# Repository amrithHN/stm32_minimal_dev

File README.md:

# stm32_minimal_dev
 
 Simple stm32f4 minimal dev board built for as part of learning hardware design using kicad 6

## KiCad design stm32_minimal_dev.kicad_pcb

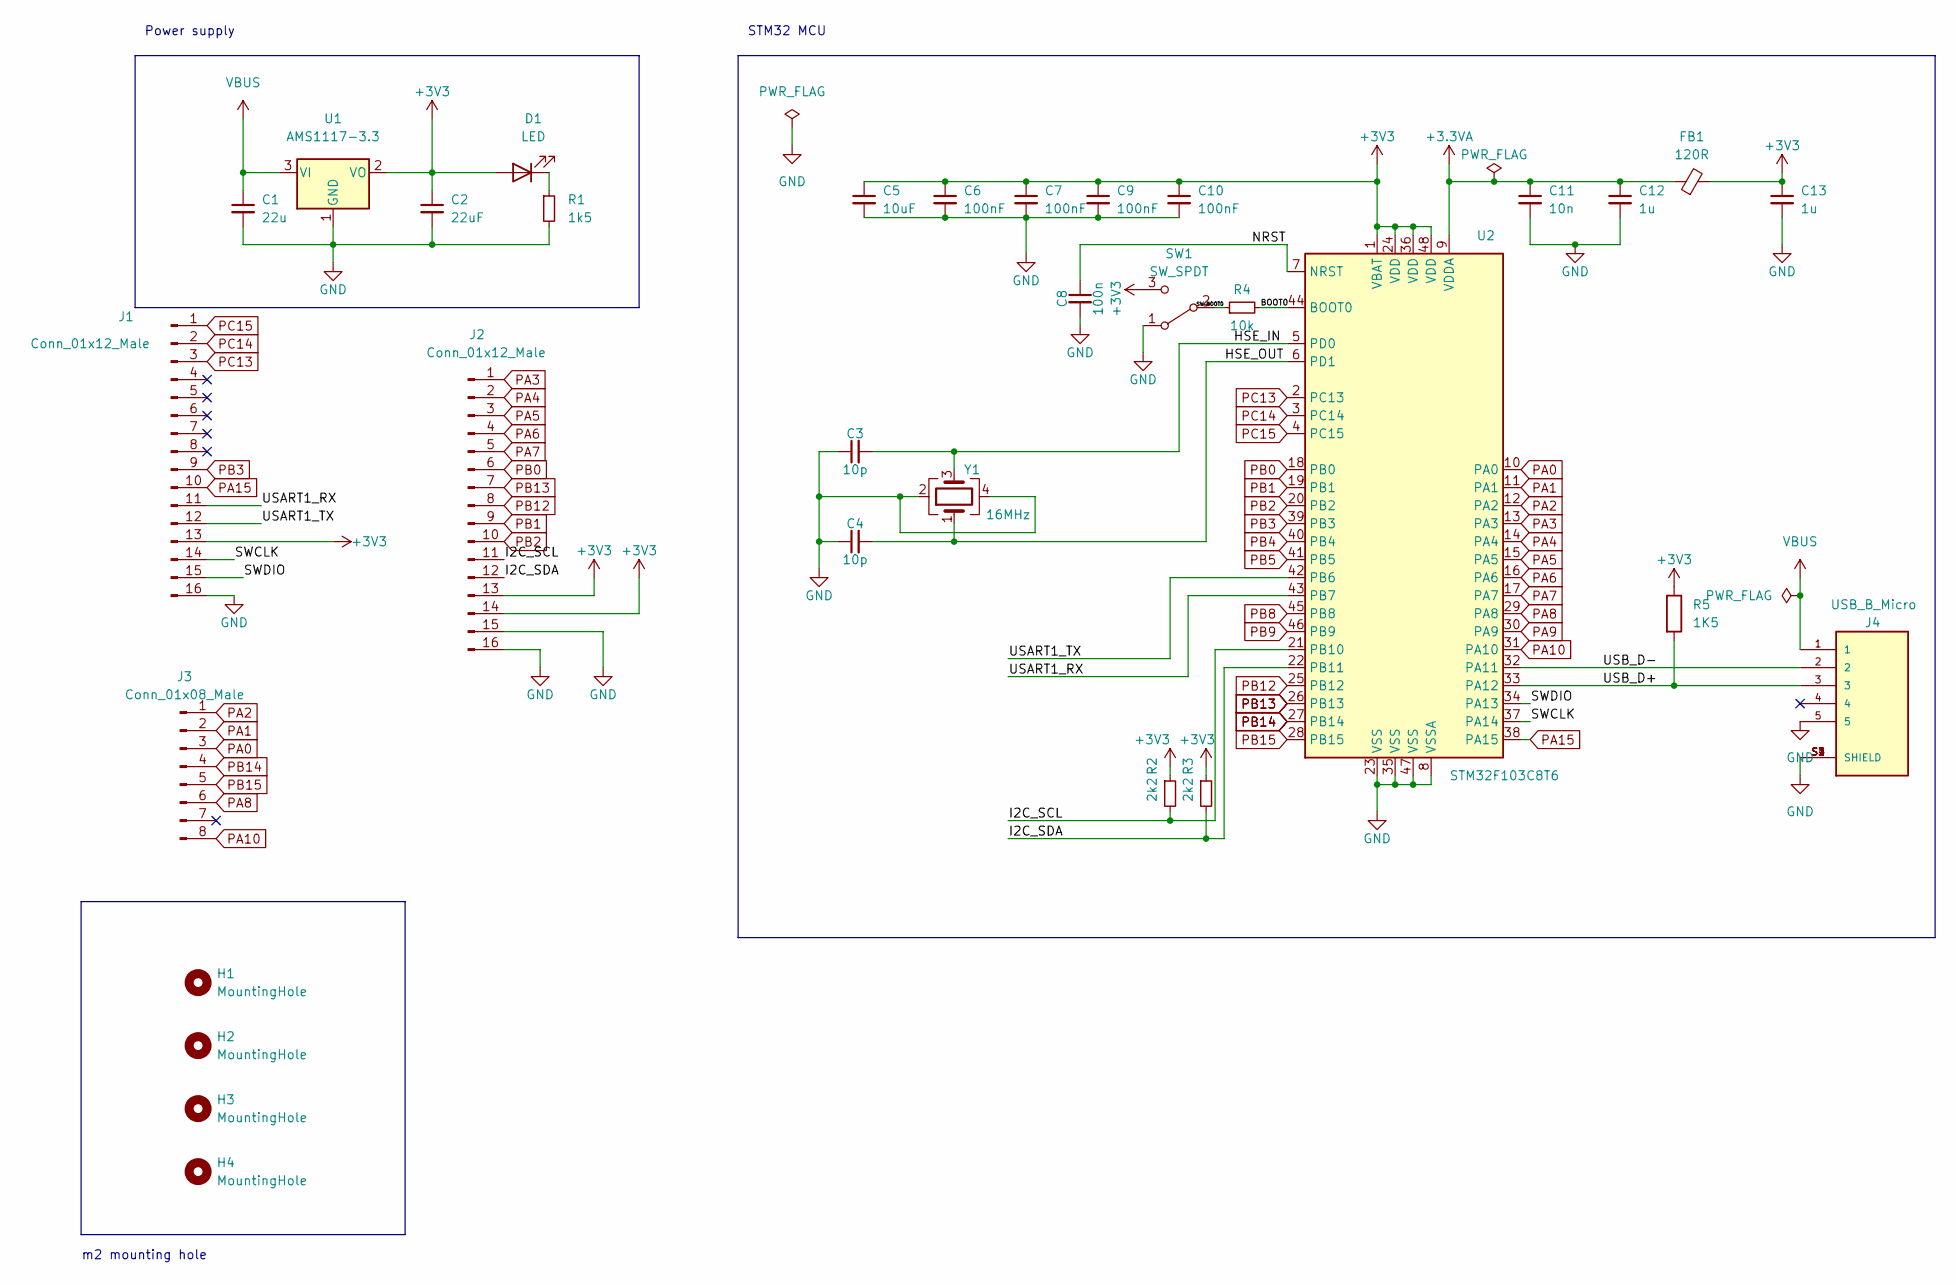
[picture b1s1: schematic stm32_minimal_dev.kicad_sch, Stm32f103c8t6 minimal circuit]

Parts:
C1: 22u; C_0805_2012Metric
C2: 22uF; C_0805_2012Metric
C3, C4: 10p; C_0402_1005Metric
C5: 10uF; C_0603_1608Metric
C6, C7, C9, C10: 100nF; C_0402_1005Metric
C8: 100n; C_0402_1005Metric
C11: 10n; C_0402_1005Metric
C12, C13: 1u; C_0402_1005Metric
D1: LED; LED_0603_1608Metric
FB1: 120R; L_0603_1608Metric
H1, H2, H3, H4: MountingHole; MountingHole_2.2mm_M2
J1, J2: Conn_01x12_Male; PinHeader_1x16_P2.54mm_Vertical
J3: Conn_01x08_Male; PinHeader_1x08_P2.54mm_Vertical
J4: USB_B_Micro; WE_629105136821; part no. 614105150721
R1: 1k5; R_0402_1005Metric
R2, R3: 2k2; R_0402_1005Metric
R4: 10k; R_0402_1005Metric
R5: 1K5; R_0402_1005Metric
SW1: SW_SPDT; SW_SPDT_PCM12
U1: AMS1117-3.3; SOT-223-3_TabPin2
U2: STM32F103C8T6; LQFP-48_7x7mm_P0.5mm
Y1: 16MHz; Crystal_SMD_3225-4Pin_3.2x2.5mm

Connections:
+3.3VA: C11.1, C12.1, FB1.1, U2.9 (VDDA)
+3V3: C2.1, C5.1, C6.1, C7.1, C9.1, C10.1, C13.1, D1.2 (A), FB1.2, J1.13, J2.13, J2.14, R2.1, R3.1, R5.1, SW1.3 (C), U1.2 (VO), U2.1 (VBAT), U2.24 (VDD), U2.36 (VDD), U2.48 (VDD)
/BOOT0: R4.2, U2.44 (BOOT0)
/HSE_IN: C3.2, U2.5 (PD0), Y1.3
/HSE_OUT: C4.2, U2.6 (PD1), Y1.1
/I2C_SCL: J2.11, R2.2, U2.21 (PB10)
/I2C_SDA: J2.12, R3.2, U2.22 (PB11)
/NRST: C8.1, U2.7 (NRST)
/SWCLK: J1.14, U2.37 (PA14)
/SWDIO: J1.15, U2.34 (PA13)
/SW_BOOT0: R4.1, SW1.2 (B)
/USART1_RX: J1.11, U2.43 (PB7)
/USART1_TX: J1.12, U2.42 (PB6)
/USB_D+: J4.3, R5.2, U2.33 (PA12)
/USB_D-: J4.2, U2.32 (PA11)
GND: C1.2, C2.2, C3.1, C4.1, C5.2, C6.2, C7.2, C8.2, C9.2, C10.2, C11.2, C12.2, C13.2, J1.16, J2.15, J2.16, J4.5, J4.S1 (SHIELD), J4.S2 (SHIELD), J4.S3 (SHIELD), J4.S4 (SHIELD), R1.2, SW1.1 (A), U1.1 (GND), U2.8 (VSSA), U2.23 (VSS), U2.35 (VSS), U2.47 (VSS), Y1.2, Y1.4
unnamed: D1.1 (K), R1.1
PA0: J3.3, U2.10 (PA0)
PA1: J3.2, U2.11 (PA1)
PA2: J3.1, U2.12 (PA2)
PA3: J2.1, U2.13 (PA3)
PA4: J2.2, U2.14 (PA4)
PA5: J2.3, U2.15 (PA5)
PA6: J2.4, U2.16 (PA6)
PA7: J2.5, U2.17 (PA7)
PA8: J3.6, U2.29 (PA8)
PA9: U2.30 (PA9)
PA10: J3.8, U2.31 (PA10)
PA15: J1.10, U2.38 (PA15)
PB0: J2.6, U2.18 (PB0)
PB1: J2.9, U2.19 (PB1)
PB2: J2.10, U2.20 (PB2)
PB3: J1.9, U2.39 (PB3)
PB4: U2.40 (PB4)
PB5: U2.41 (PB5)
PB8: U2.45 (PB8)
PB9: U2.46 (PB9)
PB12: J2.8, U2.25 (PB12)
PB13: J2.7, U2.26 (PB13)
PB14: J3.4, U2.27 (PB14)
PB15: J3.5, U2.28 (PB15)
PC13: J1.3, U2.2 (PC13)
PC14: J1.2, U2.3 (PC14)
PC15: J1.1, U2.4 (PC15)
VBUS: C1.1, J4.1, U1.3 (VI)

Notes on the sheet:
m2 mounting hole
Power supply
STM32 MCU

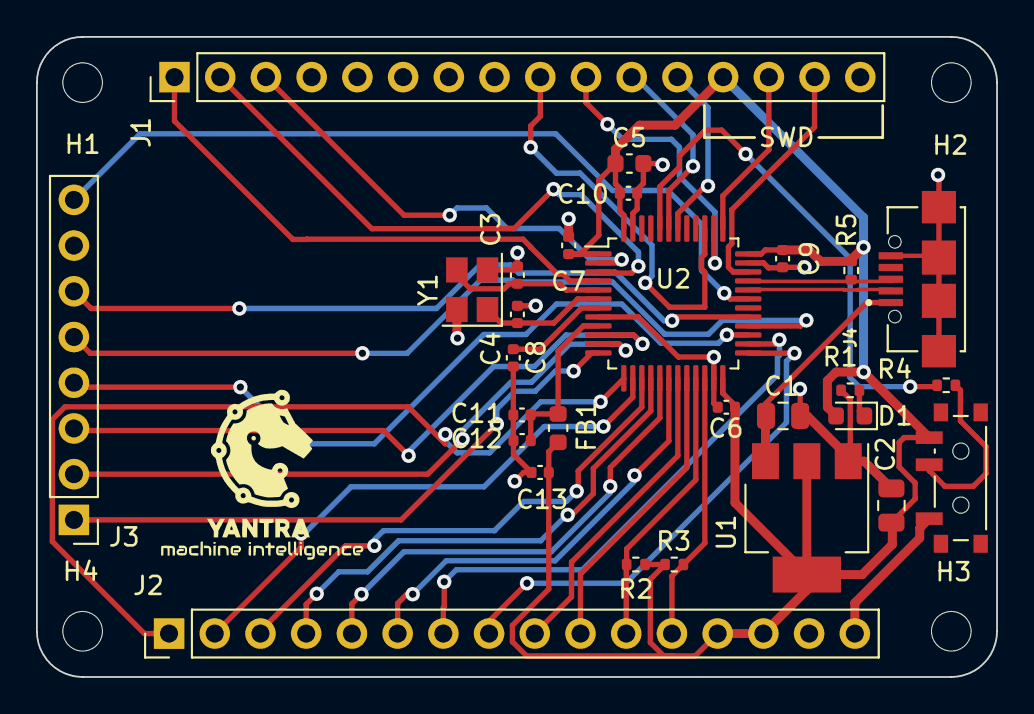
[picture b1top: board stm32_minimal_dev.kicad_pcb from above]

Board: 2 copper layers, 53.3 x 35.6 mm, 32 parts (0 on the bottom side), 40 nets.

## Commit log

2022-07-11 fix some stuff
    fixes drc errors
2022-07-12 fixes
    fix
2022-11-11 added image
2022-11-29 updated files
